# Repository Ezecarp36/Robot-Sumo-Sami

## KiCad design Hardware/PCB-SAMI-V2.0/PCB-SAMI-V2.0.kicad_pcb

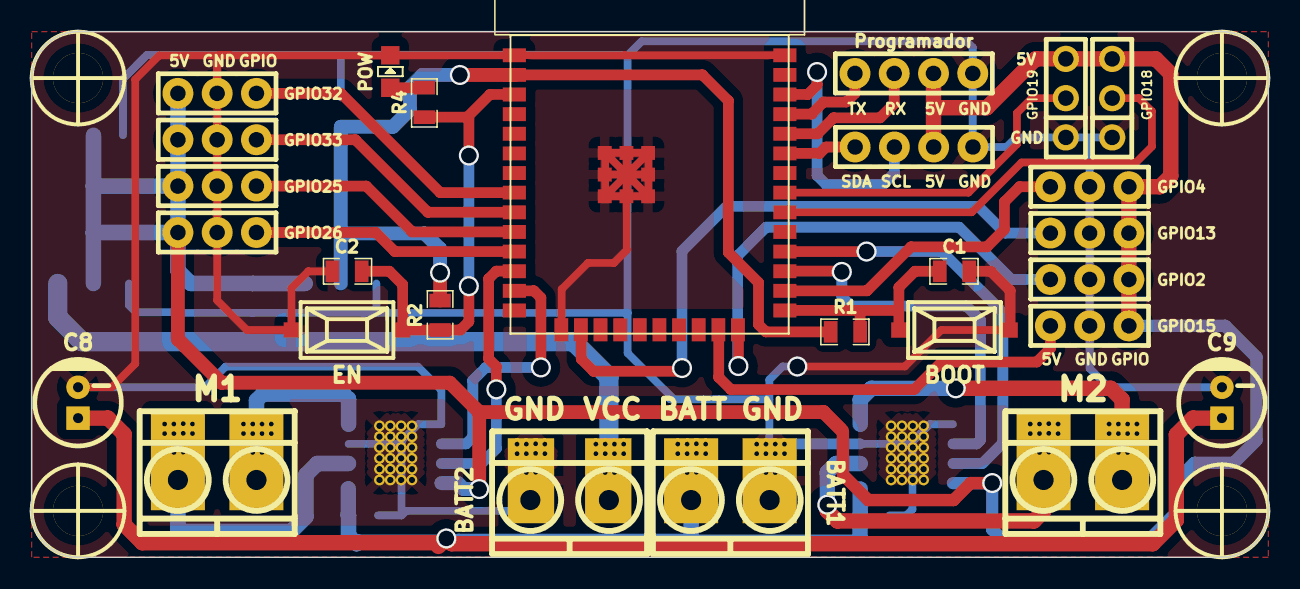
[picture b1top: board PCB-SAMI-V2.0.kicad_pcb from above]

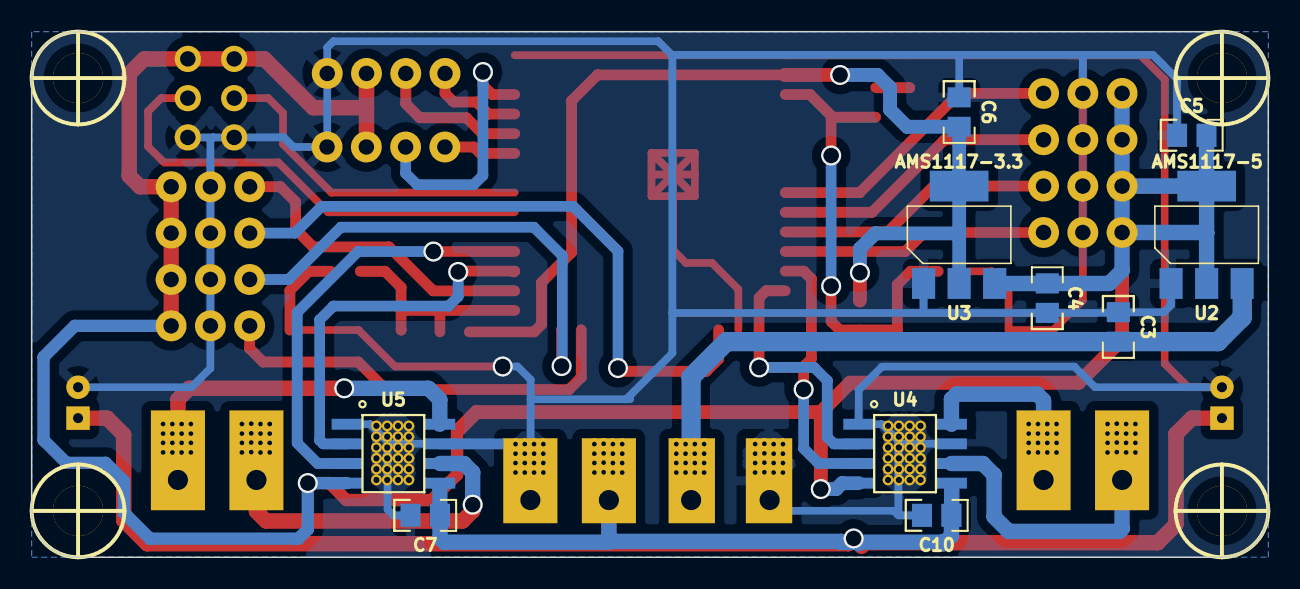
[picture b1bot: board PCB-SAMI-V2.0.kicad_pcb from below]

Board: 2 copper layers, 80.0 x 34.0 mm, 41 parts (10 on the bottom side), 30 nets.

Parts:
BOOT1: SW_Push; Pulsador_SMD_2_ALTO
C1, C2: 1n; R_0805
C3, C4, C5, C6: 10uF; C_0805
C7, C10: 100nf; C_0805
C8, C9: 100Uf/30V; CAP_ELEC_5x11mm
EN1: SW_Push; Pulsador_SMD_2_ALTO
J1: SensorAdicional_1; Pin_Strip_3
J2, J7: LDR; Pin_Strip_3
J3: QRE1113_Derecho; Pin_Strip_3
J4: IFR_DER; Pin_Strip_3
J5: NeoPixel; Pin_Strip_3
J6: SWITCH; Pin_Strip_3
J8: QRE1113_Izquierdo; Pin_Strip_3
J9: IFR_IZQ; Pin_Strip_3
J10: SensorAdicional_2; Pin_Strip_3
J11: SalidaI2C; Pin_Strip_4
J12: Bateria_6s; BORNERA2_AZUL_VIAS
J13: Bateria_3s; BORNERA2_AZUL_VIAS
J14: M1; BORNERA2_AZUL_VIAS
J15: M2; BORNERA2_AZUL_VIAS
J16: Programador; Pin_Strip_4
P2, P2#2, P2#3, P2#4: Mounting_Hole; Separador_M3_5mm
POW1: 2V; Led_0805
R1: 1OK; R_0805
R2: 10K; R_0805
R4: 470; R_0805
U1: ESP32-WROOM-32; ESP32-WROOM-32E
U2: AMS1117-5; AMS117-SOT-223
U3: AMS1117-3.3; AMS117-SOT-223
U4, U5: TB67H451AFNG; TB67H451AFNG_Disipado

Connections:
+3V3: C6.1, R1.2, R2.2, U1.3V3, U3.2 (VO)
+5V: C4.1, C5.1, J1.1, J2.1, J3.1, J4.1, J5.3, J6.3, J7.1, J8.1, J9.1, J10.1, J11.3, J16.2, U2.2 (VO), U3.3 (VI), U4.4 (VREF), U5.4 (VREF)
+BATT: C7.1, C8.1, C9.1, C10.1, J12.1, U4.5 (VM), U5.5 (VM)
/EN: C2.2, EN1.2, R2.1, R4.2, U1.9 (EN)
/IO0: BOOT1.2, C1.2, R1.1, U1.23 (IO0)
/IR_DER: J4.3, U1.15 (IO26)
/IR_IZQ: J9.3, U1.22 (IO2)
/LDR_DER: J2.3, U1.13 (IO33)
/LDR_IZQ: J7.3, U1.24 (IO4)
/M1_IN1: U1.16 (IO27), U4.3 (IN1)
/M1_IN2: U1.17 (IO14), U4.2 (IN2)
/M2_IN1: U1.27 (IO17), U5.3 (IN1)
/M2_IN2: U1.25 (IO16), U5.2 (IN2)
/NeoPixel: J5.2, U1.38 (IO19)
/OUT_A_M1: J14.2, U4.8 (OUT2)
/OUT_A_M2: J15.2, U5.8 (OUT2)
/OUT_B_M1: J14.1, U4.6 (OUT1)
/OUT_B_M2: J15.1, U5.6 (OUT1)
/Pulsador: J6.2, U1.35 (IO18)
/RXD0: J16.3, U1.40 (RXD0)
/SCL: J11.2, U1.39 (IO22)
/SDA: J11.1, U1.42 (IO21)
/SensorAd_1: J1.3, U1.12 (IO32)
/SensorAd_2: J10.3, U1.21 (IO15)
/TATAMI_DER: J3.3, U1.14 (IO25)
/TATAMI_IZQ: J8.3, U1.20 (IO13)
/TXD0: J16.4, U1.41 (TXD0)
GND: BOOT1.1, C1.1, C2.1, C3.2, C4.2, C5.2, C6.2, C7.2, C8.2, C9.2, C10.2, EN1.1, J1.2, J2.2, J3.2, J4.2, J5.1, J6.1, J7.2, J8.2, J9.2, J10.2, J11.4, J12.2, J13.1, J16.1, POW1.2 (K), U1.GND, U2.1 (GND), U3.1 (GND), U4.1 (GND), U4.7 (RS), U5.1 (GND), U5.7 (RS)
unnamed: POW1.1 (A), R4.1
VCC: C3.1, J13.2, U2.3 (VI)

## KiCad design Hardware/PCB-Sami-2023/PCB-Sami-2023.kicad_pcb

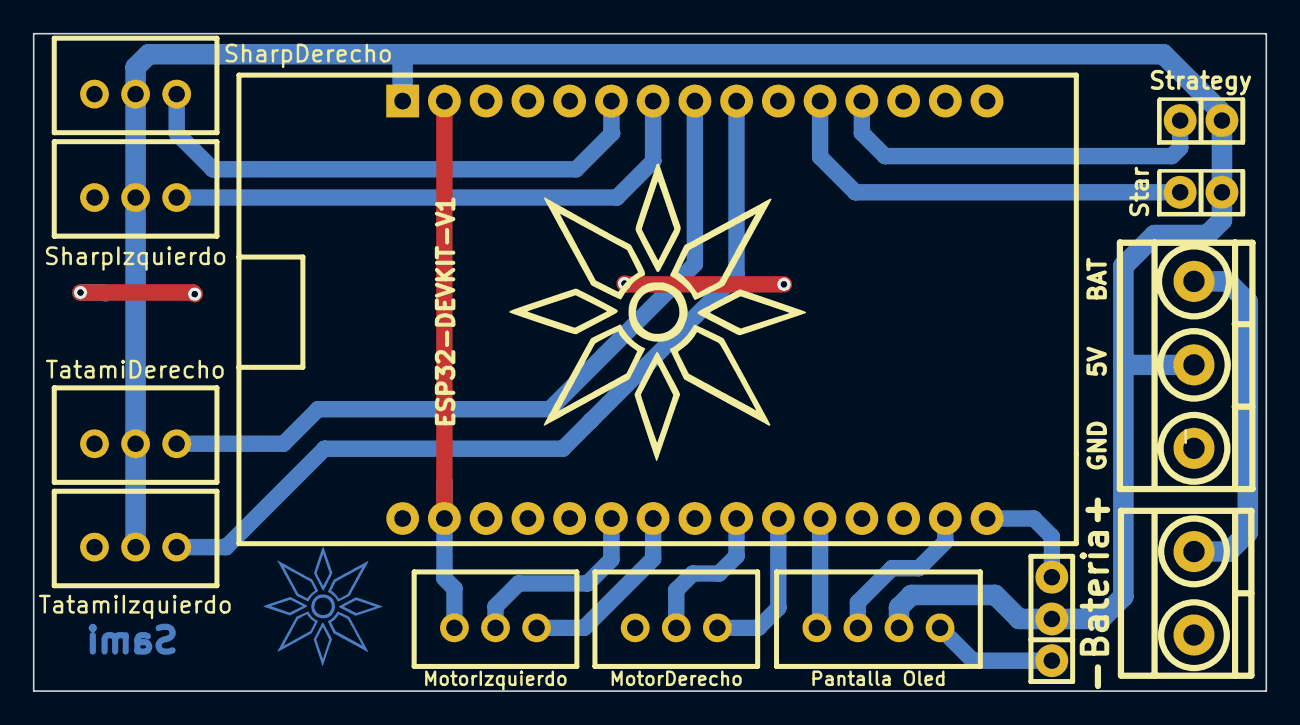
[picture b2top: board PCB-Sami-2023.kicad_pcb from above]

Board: 2 copper layers, 75.0 x 40.0 mm, 14 parts (0 on the bottom side), 16 nets.

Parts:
G1: LOGO; LogoSami2
J9: STEP_DOWN; BORNERA3_AZUL
J10: Bateria; BORNERA2_AZUL
P1: TatamiDerecho; JstXH3P
P2: TatamiIzquierdo; JstXH3P
P3: SharpDerecho; JstXH3P
P4: SharpIzquierdo; JstXH3P
P5: LDR; Pin_Strip_3
P6: MotorIzquierdo; JstXH3P
P7: MotorDerecho; JstXH3P
P8: Pantalla Oled; JstXH4P
Star: ESTRATEGIA; Pin_Header_2
Strategy: START; Pin_Header_2
U1: ESP32-DEVKIT-V1; ESP32-DEVKIT-V1-30Pines

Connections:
+5V: J9.2, P1.2, P2.2, P3.2, P4.2, P5.2, P8.3, Star.1, Strategy.1, U1.1 (VIN)
/ESTRATEGIA: Star.2, U1.11 (D35)
/IR_DER: P3.3, U1.6 (D27)
/IR_IZQ: P4.3, U1.7 (D26)
/LDR: P5.3, U1.16 (D23)
/M1A_DIR: P6.2, U1.25 (RX2)
/M1B_PWM: P6.3, U1.24 (TX2)
/M2A_DIR: P7.2, U1.22 (D18)
/M2B_PWM: P7.3, U1.21 (D19)
/SCL: P8.2, U1.17 (D22)
/SDA: P8.1, U1.20 (D21)
/START: Strategy.2, U1.12 (D34)
/TATAMI_DER: P1.3, U1.8 (D25)
/TATAMI_IZQ: P2.3, U1.9 (D33)
/Vstep: J9.3, J10.2
GND: J9.1, J10.1, P1.1, P2.1, P3.1, P4.1, P5.1, P6.1, P7.1, P8.4, U1.2 (GND), U1.29 (GND)

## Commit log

2023-04-19 Todas las librerias de los sensores y drivers agregadas y los codigos de pruebas terminados. Los del driver y sensores de distancia fueron probados, solo falta calibrar los de distancia y probar el r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
2023-04-20 modifique las pruebas de giro para utilizarlas con un menu y agregue las pruebas avance y retroceso
2023-04-21 Menu probados y funcionando
2023-04-21 agregue el esquematico de la nueva version del PCB
2023-04-30 PCB con sus componentes correctamente acomodados, falta solo los agujeros de sujecion y trazar pistas
2023-04-30 placa terminada
2023-04-30 PCB terminado
2023-05-05 Corregi algunos errores de la placa
2023-05-07 agregue el svg para la fabricacion del pcb
2023-05-07 agregue el archivo svg para la seligrafia
2023-05-08 agregue ultimos detalles
2023-05-09 cambie la programacion de pantalla oled
2023-06-19 Cambie la declaración de los pines de la motores por los correctos y realice una correccion de errores a los codigos de prueba
2023-06-19 Termine el codigo final de Sami, solo falta probarlo y corregir detalles
2023-06-21 realice un cambio en la libreria del boton
2023-06-24 Cambio en el pinout de los motores y unas correcciones de codigos luego de probar el robots
2023-07-13 agregue un codigo para usar cuando se rompe la pantalla oled y otro para el robot sin ldr, ademas de corregir un par de cosas
2023-07-29 cambios finales antes de competir
2023-09-17 correcciones en el codigo
2023-09-27 agrego 3d
2023-10-03 correccion de errores
2023-10-04 correccion de algunos errores
2023-10-06 modificaciones finales al codigo antes de la LNR
2023-10-10 termine el esquematico del nuevo PCB de Sami
2024-04-09 modificaciones en una libreria
2024-04-09 alimine 3d innecesarios
2024-04-09 agregue la version nueva del PCB de Sami
2024-04-11 empece con el codigo del control para manejar al robot
